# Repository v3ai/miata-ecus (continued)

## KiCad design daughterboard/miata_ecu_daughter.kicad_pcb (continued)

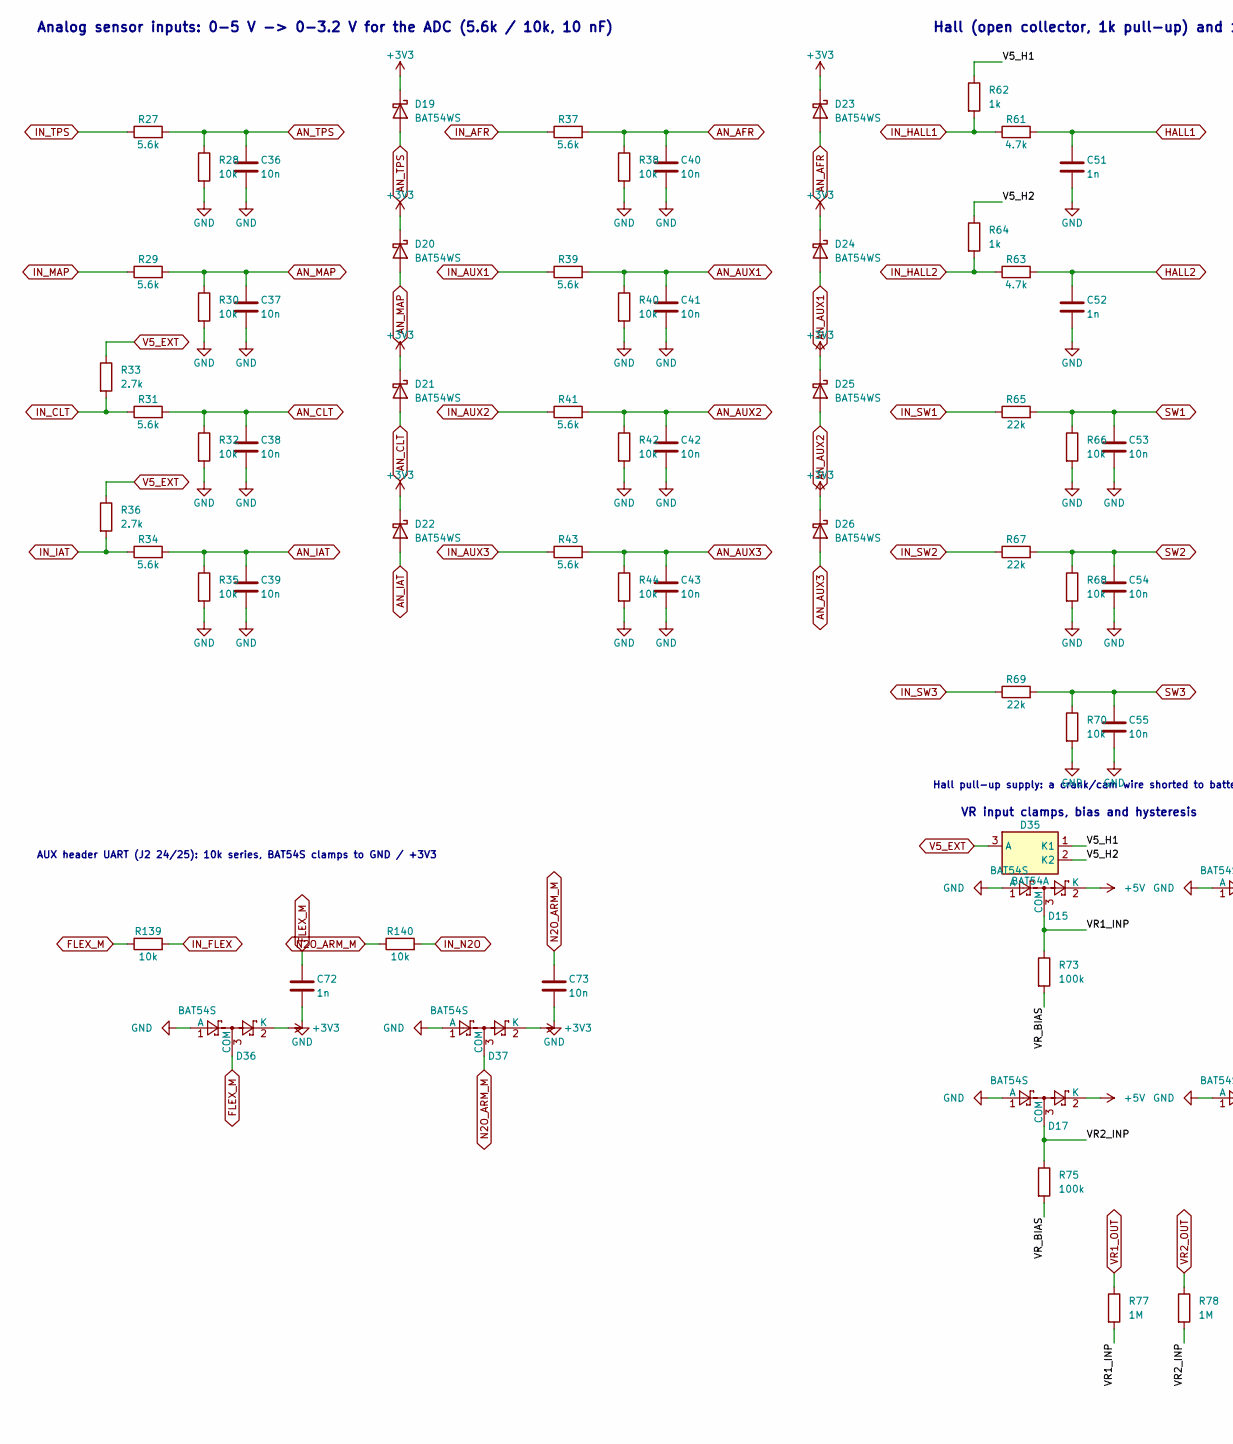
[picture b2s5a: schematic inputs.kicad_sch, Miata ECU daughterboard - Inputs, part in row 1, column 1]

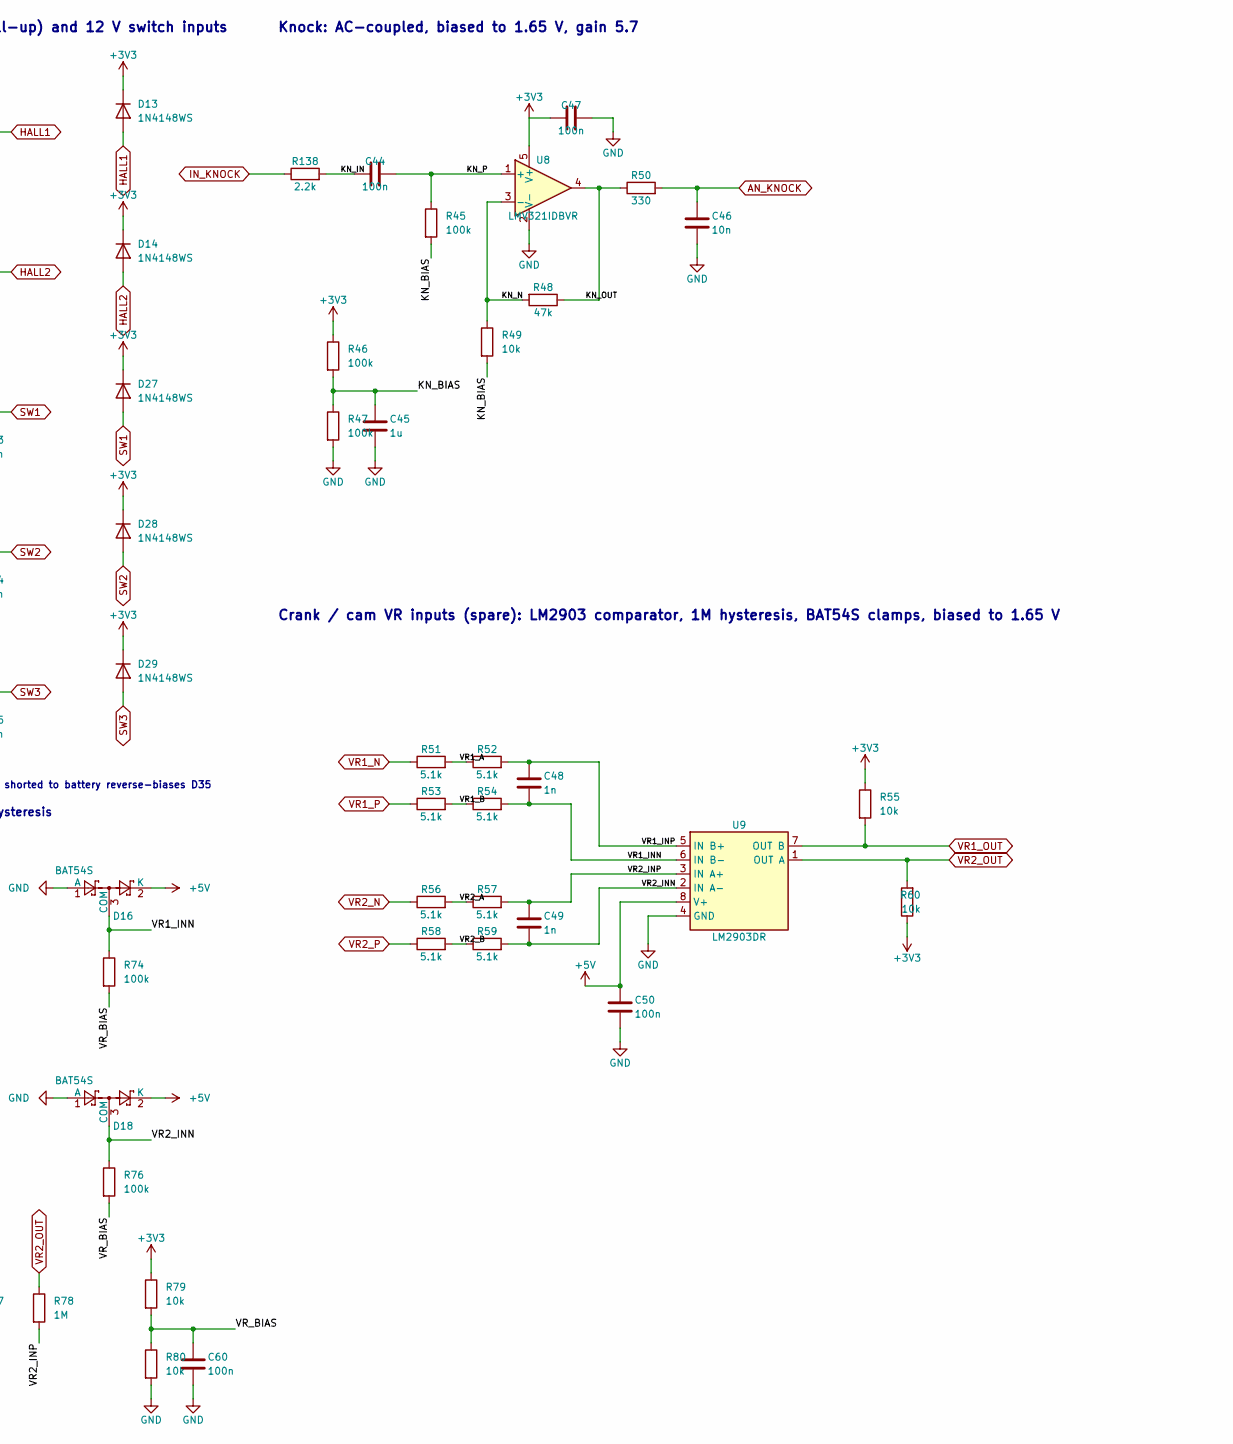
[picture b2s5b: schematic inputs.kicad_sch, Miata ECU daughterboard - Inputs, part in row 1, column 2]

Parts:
C36, C37, C38, C39, C40, C41, C42, C43, C53, C54, C55, C73: 10n; C_0402_1005Metric; LCSC C15195
C44, C47, C50: 100n; C_0603_1608Metric; LCSC C14663
C45: 1u; C_0603_1608Metric; LCSC C15849
C46: 10n; C_0603_1608Metric; LCSC C57112
C48, C49: 1n; C_0805_2012Metric; LCSC C46653
C51, C52, C72: 1n; C_0402_1005Metric; LCSC C1523
C60: 100n; C_0402_1005Metric; LCSC C1525
D13, D14, D27, D28, D29: 1N4148WS; D_SOD-323; LCSC C2128
D15, D16, D17, D18, D36, D37: BAT54S; SOT-23; LCSC C19726
D19, D20, D21, D22, D23, D24, D25, D26: BAT54WS; D_SOD-323; LCSC C124205
D35: BAT54A; SOT-23; LCSC C916423
R27, R29, R31, R34, R37, R39, R41, R43: 5.6k; R_0603_1608Metric; LCSC C23189
R28, R30, R32, R35, R38, R40, R42, R44, R66, R68, R70, R79, R80: 10k; R_0402_1005Metric; LCSC C25744
R33, R36: 2.7k; R_0603_1608Metric; LCSC C13167
R45, R46, R47: 100k; R_0603_1608Metric; LCSC C25803
R48: 47k; R_0603_1608Metric; LCSC C25819
R49, R55, R60, R139, R140: 10k; R_0603_1608Metric; LCSC C25804
R50: 330; R_0603_1608Metric; LCSC C23138
R51, R52, R53, R54, R56, R57, R58, R59: 5.1k; R_0805_2012Metric; LCSC C27834
R61, R63: 4.7k; R_0603_1608Metric; LCSC C23162
R62, R64: 1k; R_0603_1608Metric; LCSC C21190
R65, R67, R69: 22k; R_0402_1005Metric; LCSC C25768
R73, R74, R75, R76: 100k; R_0402_1005Metric; LCSC C25741
R77, R78: 1M; R_0402_1005Metric; LCSC C26083
R138: 2.2k; R_0402_1005Metric; LCSC C25879
U8: LMV321IDBVR; SOT-23-5; LCSC C7972
U9: LM2903DR; SOIC-8_3.9x4.9mm_P1.27mm; LCSC C7549

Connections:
+3V3: C47.1, D13.1 (K), D14.1 (K), D19.1 (K), D20.1 (K), D21.1 (K), D22.1 (K), D23.1 (K), D24.1 (K), D25.1 (K), D26.1 (K), D27.1 (K), D28.1 (K), D29.1 (K), D36.2 (K), D37.2 (K), R46.1, R55.1, R60.1, R79.1, U8.5 (V+); also elsewhere on the board
+5V: C50.1, D15.2 (K), D16.2 (K), D17.2 (K), D18.2 (K), U9.8 (V+); also elsewhere on the board
/Inputs/KN_BIAS: C45.1, R45.2, R46.2, R47.1, R49.2
/Inputs/KN_IN: C44.1, R138.2
/Inputs/KN_N: R48.2, R49.1, U8.3 (-)
/Inputs/KN_OUT: R48.1, R50.1, U8.4
/Inputs/KN_P: C44.2, R45.1, U8.1 (+)
/Inputs/V5_H1: D35.1 (K1), R62.1
/Inputs/V5_H2: D35.2 (K2), R64.1
/Inputs/VR1_A: R51.2, R52.1
/Inputs/VR1_B: R53.2, R54.1
/Inputs/VR1_INN: C48.2, D16.3 (COM), R54.2, R74.1, U9.6 (IN B-)
/Inputs/VR1_INP: C48.1, D15.3 (COM), R52.2, R73.1, R77.2, U9.5 (IN B+)
/Inputs/VR2_A: R56.2, R57.1
/Inputs/VR2_B: R58.2, R59.1
/Inputs/VR2_INN: C49.2, D18.3 (COM), R59.2, R76.1, U9.2 (IN A-)
/Inputs/VR2_INP: C49.1, D17.3 (COM), R57.2, R75.1, R78.2, U9.3 (IN A+)
/Inputs/VR_BIAS: C60.1, R73.2, R74.2, R75.2, R76.2, R79.2, R80.1
AN_AFR: C40.1, D23.2 (A), R37.2, R38.1; also elsewhere on the board
AN_AUX1: C41.1, D24.2 (A), R39.2, R40.1; also elsewhere on the board
AN_AUX2: C42.1, D25.2 (A), R41.2, R42.1; also elsewhere on the board
AN_AUX3: C43.1, D26.2 (A), R43.2, R44.1; also elsewhere on the board
AN_CLT: C38.1, D21.2 (A), R31.2, R32.1; also elsewhere on the board
AN_IAT: C39.1, D22.2 (A), R34.2, R35.1; also elsewhere on the board
AN_KNOCK: C46.1, R50.2; also elsewhere on the board
AN_MAP: C37.1, D20.2 (A), R29.2, R30.1; also elsewhere on the board
AN_TPS: C36.1, D19.2 (A), R27.2, R28.1; also elsewhere on the board
FLEX_M: C72.1, D36.3 (COM), R139.1; also elsewhere on the board
GND: C36.2, C37.2, C38.2, C39.2, C40.2, C41.2, C42.2, C43.2, C45.2, C46.2, C47.2, C50.2, C51.2, C52.2, C53.2, C54.2, C55.2, C60.2, C72.2, C73.2, D15.1 (A), D16.1 (A), D17.1 (A), D18.1 (A), D36.1 (A), D37.1 (A), R28.2, R30.2, R32.2, R35.2, R38.2, R40.2, R42.2, R44.2, R47.2, R66.2, R68.2, R70.2, R80.2, U8.2 (V-), U9.4 (GND); also elsewhere on the board
HALL1: C51.1, D13.2 (A), R61.2; also elsewhere on the board
HALL2: C52.1, D14.2 (A), R63.2; also elsewhere on the board
IN_AFR: R37.1; also elsewhere on the board
IN_AUX1: R39.1; also elsewhere on the board
IN_AUX2: R41.1; also elsewhere on the board
IN_AUX3: R43.1; also elsewhere on the board
IN_CLT: R31.1, R33.2; also elsewhere on the board
IN_FLEX: R139.2; also elsewhere on the board
IN_HALL1: R61.1, R62.2; also elsewhere on the board
IN_HALL2: R63.1, R64.2; also elsewhere on the board
IN_IAT: R34.1, R36.2; also elsewhere on the board
IN_KNOCK: R138.1; also elsewhere on the board
IN_MAP: R29.1; also elsewhere on the board
IN_N2O: R140.2; also elsewhere on the board
IN_SW1: R65.1; also elsewhere on the board
IN_SW2: R67.1; also elsewhere on the board
IN_SW3: R69.1; also elsewhere on the board
IN_TPS: R27.1; also elsewhere on the board
N2O_ARM_M: C73.1, D37.3 (COM), R140.1; also elsewhere on the board
SW1: C53.1, D27.2 (A), R65.2, R66.1; also elsewhere on the board
SW2: C54.1, D28.2 (A), R67.2, R68.1; also elsewhere on the board
SW3: C55.1, D29.2 (A), R69.2, R70.1; also elsewhere on the board
V5_EXT: D35.3 (A), R33.1, R36.1; also elsewhere on the board
VR1_N: R51.1; also elsewhere on the board
VR1_OUT: R55.2, R77.1, U9.7 (OUT B); also elsewhere on the board
VR1_P: R53.1; also elsewhere on the board
VR2_N: R56.1; also elsewhere on the board
VR2_OUT: R60.2, R78.1, U9.1 (OUT A); also elsewhere on the board
VR2_P: R58.1; also elsewhere on the board

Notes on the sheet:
Analog sensor inputs: 0-5 V -> 0-3.2 V for the ADC (5.6k / 10k, 10 nF)
Hall (open collector, 1k pull-up) and 12 V switch inputs
Hall pull-up supply: a crank/cam wire shorted to battery reverse-biases D35
AUX header UART (J2 24/25): 10k series, BAT54S clamps to GND / +3V3
Knock: AC-coupled, biased to 1.65 V, gain 5.7
Crank / cam VR inputs (spare): LM2903 comparator, 1M hysteresis, BAT54S clamps, biased to 1.65 V
VR input clamps, bias and hysteresis

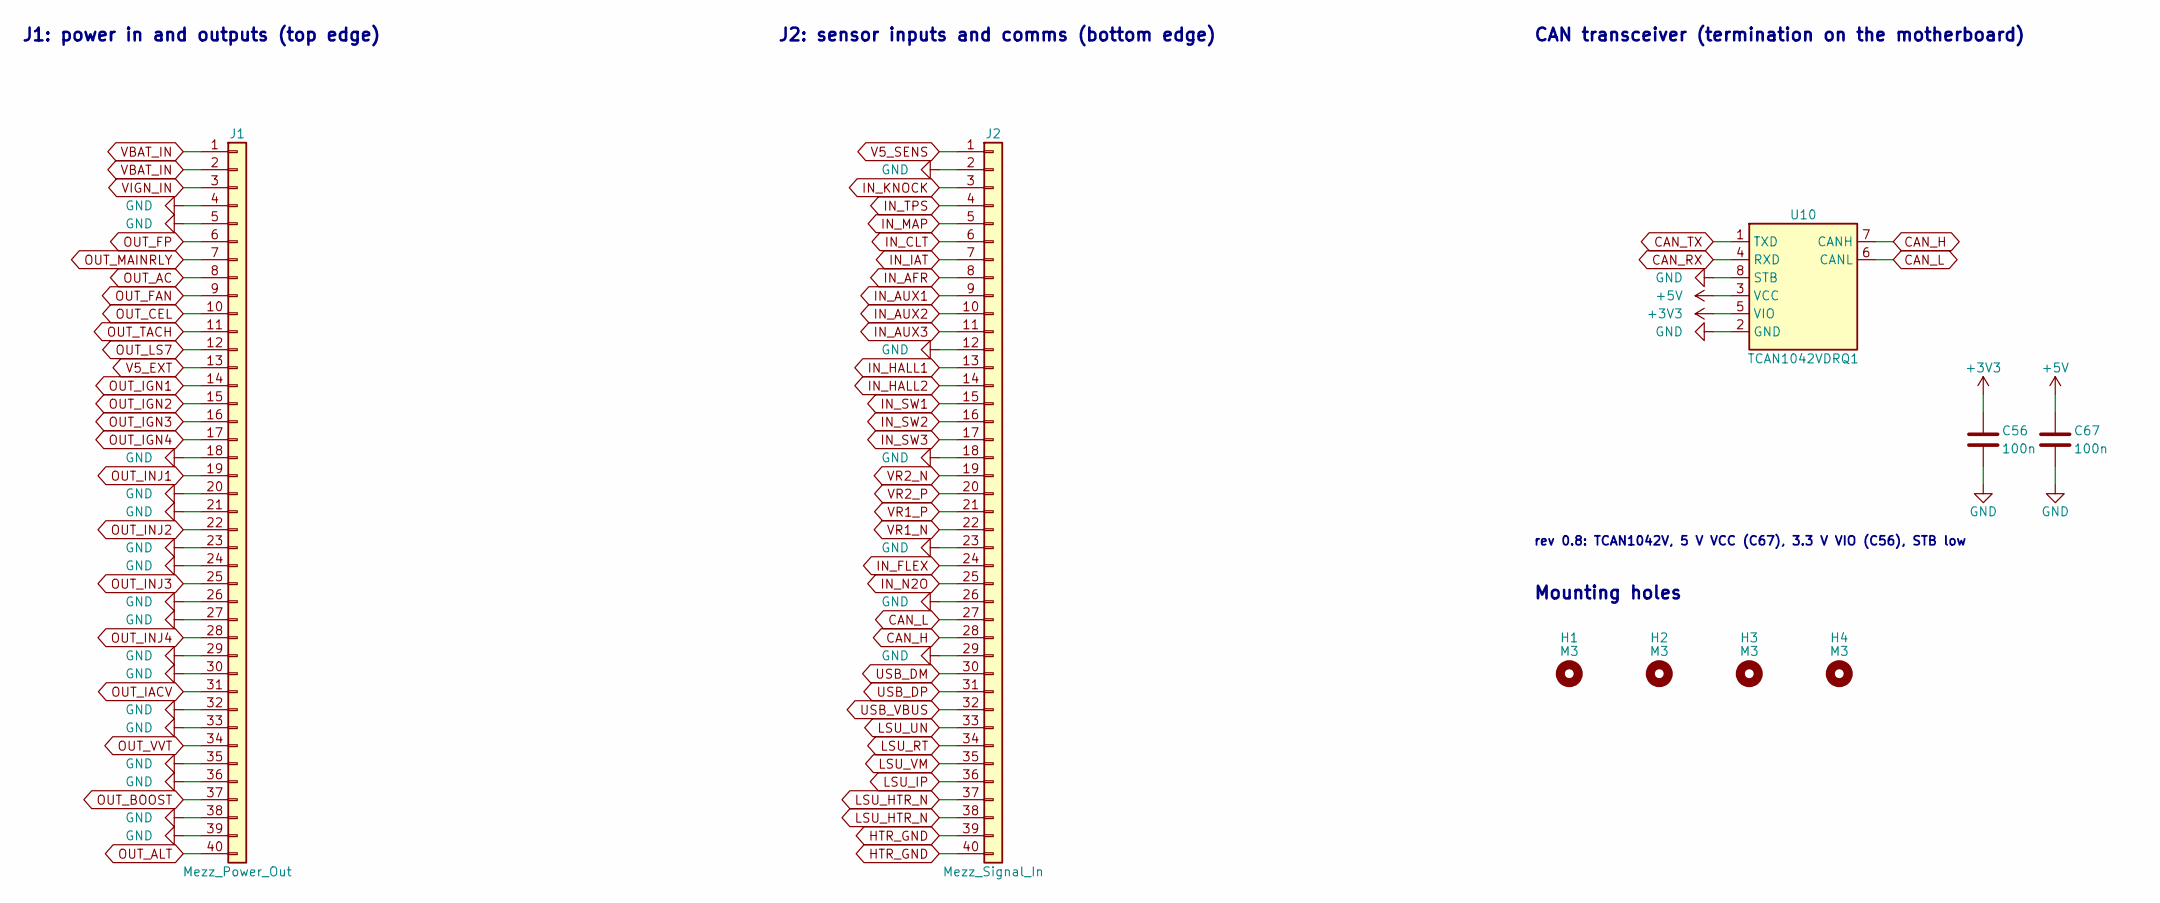
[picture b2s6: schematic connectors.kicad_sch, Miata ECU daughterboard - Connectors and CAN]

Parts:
C56: 100n; C_0603_1608Metric; LCSC C14663
C67: 100n; C_0402_1005Metric; LCSC C1525
H1, H2, H3, H4: M3; MountingHole_3.2mm_M3
J1: Mezz_Power_Out; PinHeader_1x40_P2.54mm_Vertical; LCSC C2977586
J2: Mezz_Signal_In; PinHeader_1x40_P2.54mm_Vertical; LCSC C2977586
U10: TCAN1042VDRQ1; SOIC-8_3.9x4.9mm_P1.27mm; LCSC C485806

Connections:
+3V3: C56.1, U10.5 (VIO); also elsewhere on the board
+5V: C67.1, U10.3 (VCC); also elsewhere on the board
CAN_H: J2.28, U10.7 (CANH); also elsewhere on the board
CAN_L: J2.27, U10.6 (CANL); also elsewhere on the board
CAN_RX: U10.4 (RXD); also elsewhere on the board
CAN_TX: U10.1 (TXD); also elsewhere on the board
GND: C56.2, C67.2, J1.4, J1.5, J1.18, J1.20, J1.21, J1.23, J1.24, J1.26, J1.27, J1.29, J1.30, J1.32, J1.33, J1.35, J1.36, J1.38, J1.39, J2.2, J2.12, J2.18, J2.23, J2.26, J2.29, U10.2 (GND), U10.8 (STB); also elsewhere on the board
HTR_GND: J2.39, J2.40; also elsewhere on the board
IN_AFR: J2.8; also elsewhere on the board
IN_AUX1: J2.9; also elsewhere on the board
IN_AUX2: J2.10; also elsewhere on the board
IN_AUX3: J2.11; also elsewhere on the board
IN_CLT: J2.6; also elsewhere on the board
IN_FLEX: J2.24; also elsewhere on the board
IN_HALL1: J2.13; also elsewhere on the board
IN_HALL2: J2.14; also elsewhere on the board
IN_IAT: J2.7; also elsewhere on the board
IN_KNOCK: J2.3; also elsewhere on the board
IN_MAP: J2.5; also elsewhere on the board
IN_N2O: J2.25; also elsewhere on the board
IN_SW1: J2.15; also elsewhere on the board
IN_SW2: J2.16; also elsewhere on the board
IN_SW3: J2.17; also elsewhere on the board
IN_TPS: J2.4; also elsewhere on the board
LSU_HTR_N: J2.37, J2.38; also elsewhere on the board
LSU_IP: J2.36; also elsewhere on the board
LSU_RT: J2.34; also elsewhere on the board
LSU_UN: J2.33; also elsewhere on the board
LSU_VM: J2.35; also elsewhere on the board
OUT_AC: J1.8; also elsewhere on the board
OUT_ALT: J1.40; also elsewhere on the board
OUT_BOOST: J1.37; also elsewhere on the board
OUT_CEL: J1.10; also elsewhere on the board
OUT_FAN: J1.9; also elsewhere on the board
OUT_FP: J1.6; also elsewhere on the board
OUT_IACV: J1.31; also elsewhere on the board
OUT_IGN1: J1.14; also elsewhere on the board
OUT_IGN2: J1.15; also elsewhere on the board
OUT_IGN3: J1.16; also elsewhere on the board
OUT_IGN4: J1.17; also elsewhere on the board
OUT_INJ1: J1.19; also elsewhere on the board
OUT_INJ2: J1.22; also elsewhere on the board
OUT_INJ3: J1.25; also elsewhere on the board
OUT_INJ4: J1.28; also elsewhere on the board
OUT_LS7: J1.12; also elsewhere on the board
OUT_MAINRLY: J1.7; also elsewhere on the board
OUT_TACH: J1.11; also elsewhere on the board
OUT_VVT: J1.34; also elsewhere on the board
USB_DM: J2.30; also elsewhere on the board
USB_DP: J2.31; also elsewhere on the board
USB_VBUS: J2.32; also elsewhere on the board
V5_EXT: J1.13; also elsewhere on the board
V5_SENS: J2.1; also elsewhere on the board
VBAT_IN: J1.1, J1.2; also elsewhere on the board
VIGN_IN: J1.3; also elsewhere on the board
VR1_N: J2.22; also elsewhere on the board
VR1_P: J2.21; also elsewhere on the board
VR2_N: J2.19; also elsewhere on the board
VR2_P: J2.20; also elsewhere on the board

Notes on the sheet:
J1: power in and outputs (top edge)
J2: sensor inputs and comms (bottom edge)
CAN transceiver (termination on the motherboard)
rev 0.8: TCAN1042V, 5 V VCC (C67), 3.3 V VIO (C56), STB low
Mounting holes

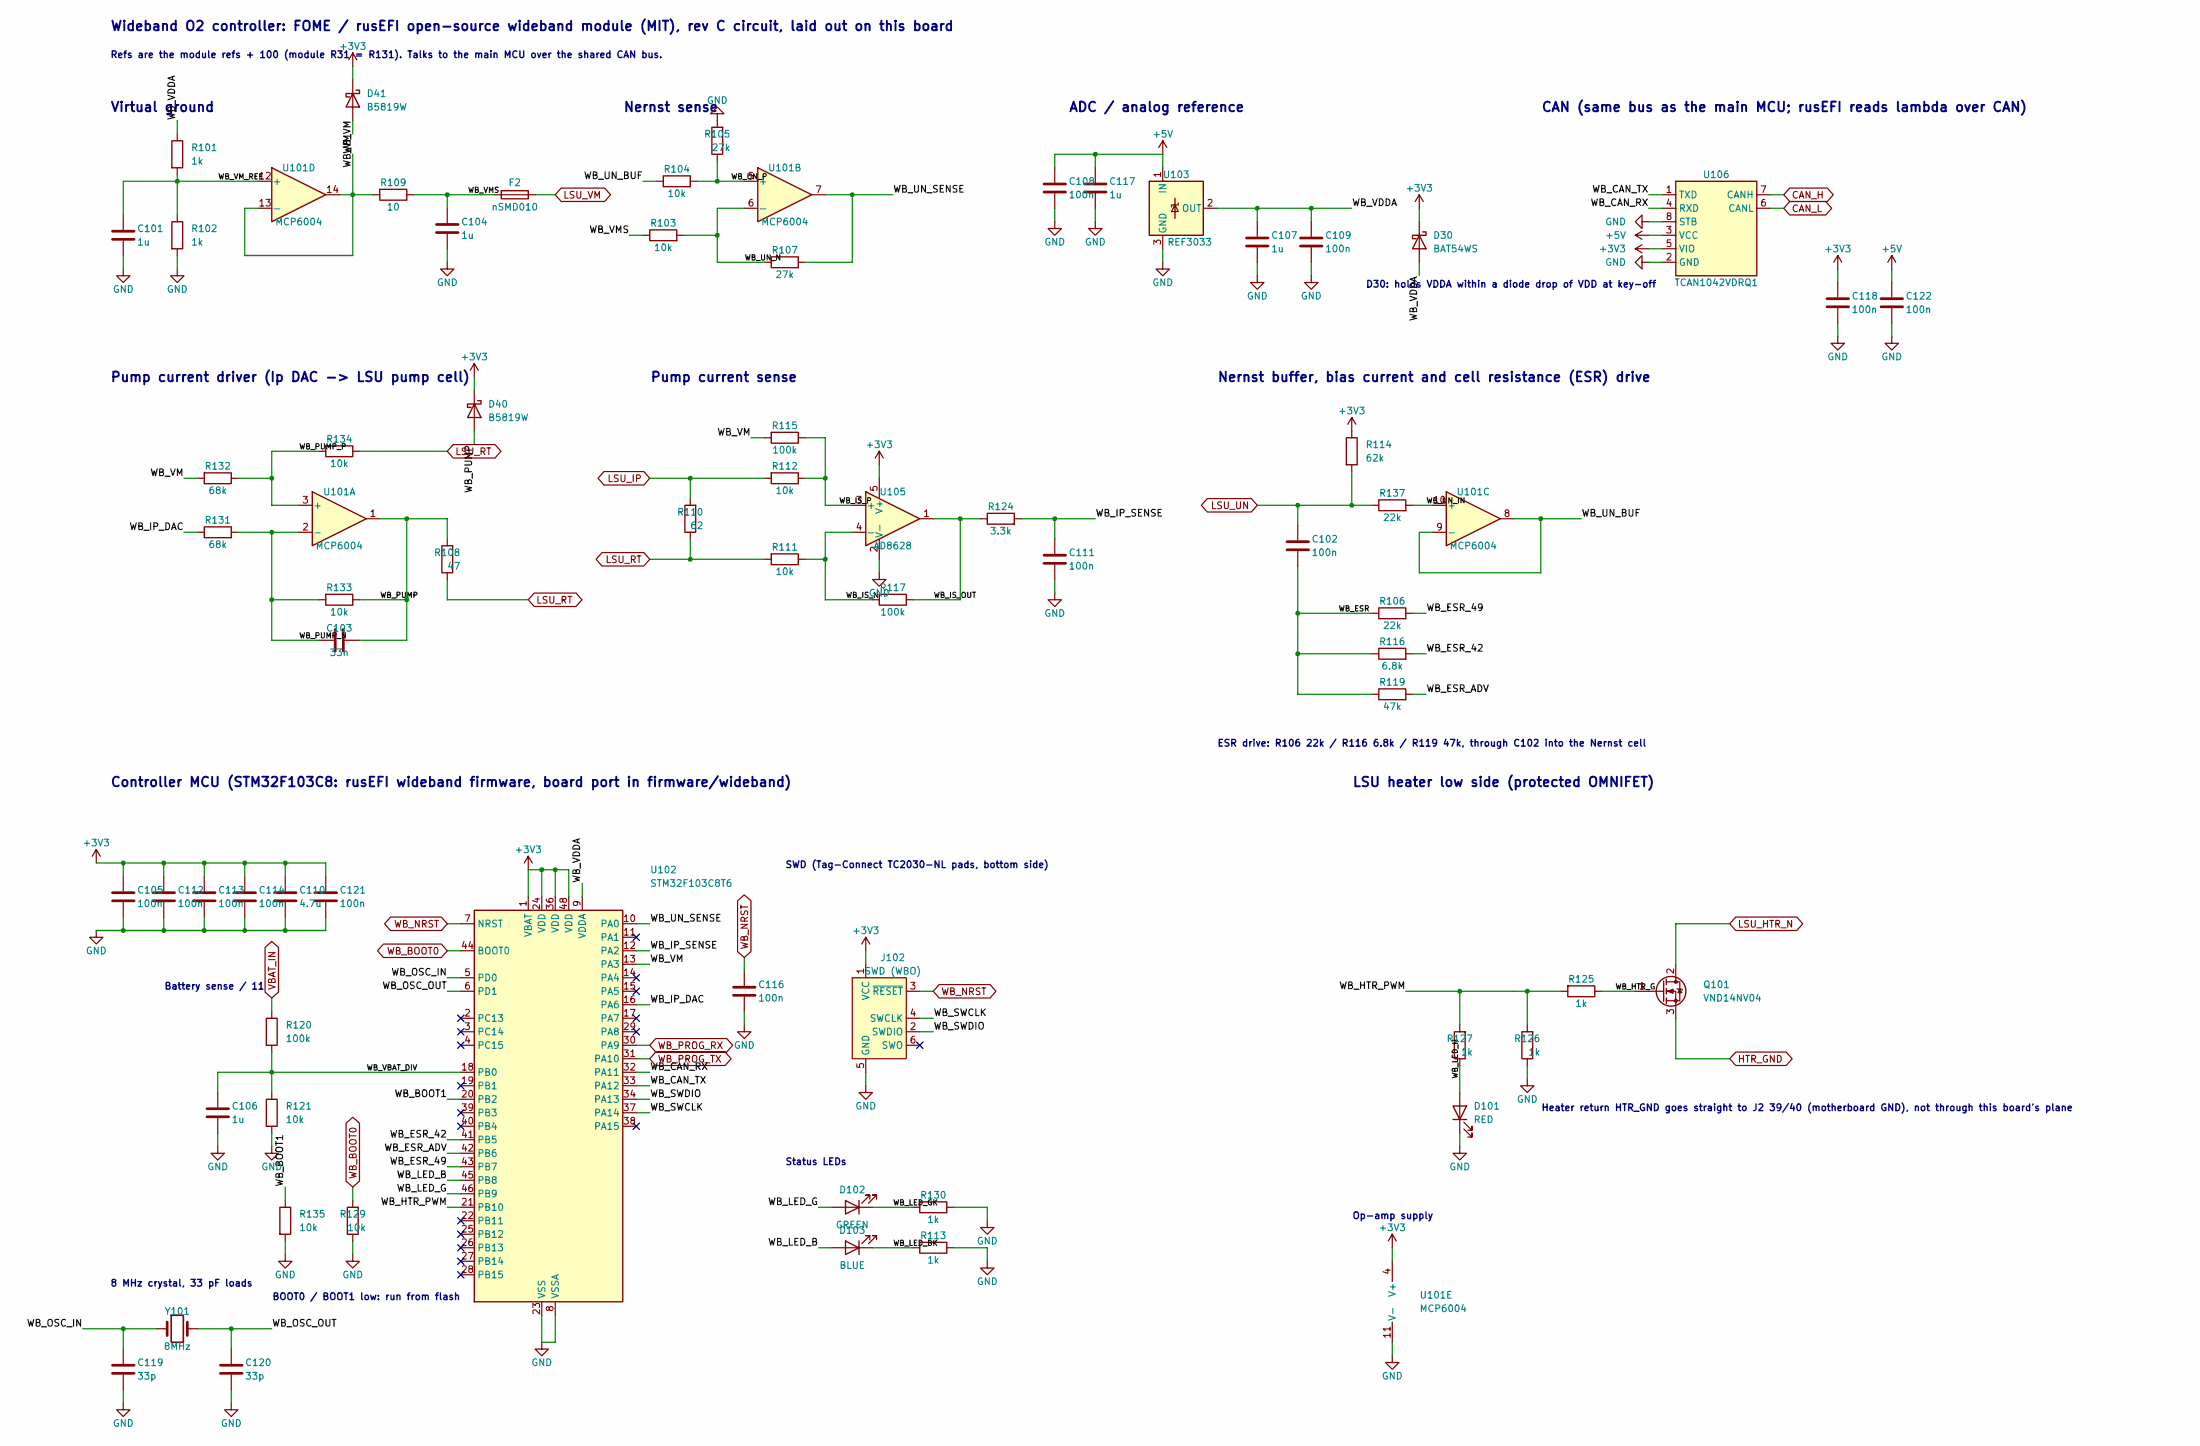
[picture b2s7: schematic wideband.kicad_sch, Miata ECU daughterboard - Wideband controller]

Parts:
C101, C104, C106, C107, C117: 1u; C_0402_1005Metric; LCSC C52923
C102, C105, C108, C109, C111, C112, C113, C114, C116, C118, C121, C122: 100n; C_0402_1005Metric; LCSC C1525
C103: 33n; C_0402_1005Metric; LCSC C106862
C110: 4.7u; C_0603_1608Metric; LCSC C19666
C119, C120: 33p; C_0402_1005Metric; LCSC C1562
D30: BAT54WS; D_SOD-323; LCSC C124205
D40, D41: B5819W; D_SOD-123; LCSC C8598
D101: RED; LED_0603_1608Metric; LCSC C2286
D102: GREEN; LED_0603_1608Metric; LCSC C12624
D103: BLUE; LED_0603_1608Metric; LCSC C2288
F2: nSMD010; Fuse_1206_3216Metric; LCSC C70065
J102: SWD (WBO); Tag-Connect_TC2030-IDC-NL_2x03_P1.27mm_Vertical
Q101: VND14NV04; TO-252-2; LCSC C2649436
R101, R102, R113, R125, R126, R127, R130: 1k; R_0402_1005Metric; LCSC C11702
R103, R104, R111, R112, R121, R129, R133, R134, R135: 10k; R_0402_1005Metric; LCSC C25744
R105, R107: 27k; R_0402_1005Metric; LCSC C25771
R106, R137: 22k; R_0402_1005Metric; LCSC C25768
R108: 47; R_1206_3216Metric; LCSC C17969
R109: 10; R_1206_3216Metric; LCSC C17903
R110: 62; R_1206_3216Metric; LCSC C25341
R114: 62k; R_0603_1608Metric; LCSC C23221
R115, R117, R120: 100k; R_0402_1005Metric; LCSC C25741
R116: 6.8k; R_0402_1005Metric; LCSC C25917
R119: 47k; R_0402_1005Metric; LCSC C25792
R124: 3.3k; R_0402_1005Metric; LCSC C25890
R131, R132: 68k; R_0402_1005Metric; LCSC C36871
U101: MCP6004; TSSOP-14_4.4x5mm_P0.65mm; LCSC C50282
U102: STM32F103C8T6; LQFP-48_7x7mm_P0.5mm; LCSC C8734
U103: REF3033; SOT-23; LCSC C36658
U105: AD8628; SOT-23-5; LCSC C29309
U106: TCAN1042VDRQ1; SOIC-8_3.9x4.9mm_P1.27mm; LCSC C485806
Y101: 8MHz; Crystal_SMD_5032-2Pin_5.0x3.2mm; LCSC C115962

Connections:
+3V3: C105.1, C110.1, C112.1, C113.1, C114.1, C118.1, C121.1, D30.1 (K), D40.1 (K), D41.1 (K), J102.1 (VCC), R114.1, U101.4 (V+), U102.1 (VBAT), U102.24 (VDD), U102.36 (VDD), U102.48 (VDD), U105.5 (V+), U106.5 (VIO); also elsewhere on the board
+5V: C108.1, C117.1, C122.1, U103.1 (IN), U106.3 (VCC); also elsewhere on the board
/Wideband controller/WB_BOOT1: R135.1, U102.20 (PB2)
/Wideband controller/WB_CAN_RX: U102.32 (PA11), U106.4 (RXD)
/Wideband controller/WB_CAN_TX: U102.33 (PA12), U106.1 (TXD)
/Wideband controller/WB_ESR: C102.2, R106.1, R116.1, R119.1
/Wideband controller/WB_ESR_42: R116.2, U102.41 (PB5)
/Wideband controller/WB_ESR_49: R106.2, U102.43 (PB7)
/Wideband controller/WB_ESR_ADV: R119.2, U102.42 (PB6)
/Wideband controller/WB_HTR_G: Q101.1 (G), R125.1
/Wideband controller/WB_HTR_PWM: R125.2, R126.2, R127.2, U102.21 (PB10)
/Wideband controller/WB_IP_DAC: R131.1, U102.16 (PA6)
/Wideband controller/WB_IP_SENSE: C111.1, R124.2, U102.12 (PA2)
/Wideband controller/WB_IS_N: R111.1, R117.2, U105.4 (-)
/Wideband controller/WB_IS_OUT: R117.1, R124.1, U105.1
/Wideband controller/WB_IS_P: R112.1, R115.1, U105.3 (+)
/Wideband controller/WB_LED_B: D103.2 (A), U102.45 (PB8)
/Wideband controller/WB_LED_BK: D103.1 (K), R113.2
/Wideband controller/WB_LED_G: D102.2 (A), U102.46 (PB9)
/Wideband controller/WB_LED_GK: D102.1 (K), R130.2
/Wideband controller/WB_LED_H: D101.2 (A), R127.1
/Wideband controller/WB_OSC_IN: C119.1, U102.5 (PD0), Y101.1
/Wideband controller/WB_OSC_OUT: C120.1, U102.6 (PD1), Y101.2
/Wideband controller/WB_PUMP: C103.1, D40.2 (A), R108.2, R133.1, U101.1
/Wideband controller/WB_PUMP_N: C103.2, R131.2, R133.2, U101.2 (-)
/Wideband controller/WB_PUMP_P: R132.1, R134.2, U101.3 (+)
/Wideband controller/WB_SWCLK: J102.4 (SWCLK), U102.37 (PA14)
/Wideband controller/WB_SWDIO: J102.2 (SWDIO), U102.34 (PA13)
/Wideband controller/WB_UN_BUF: R104.1, U101.8, U101.9 (-)
/Wideband controller/WB_UN_IN: R137.2, U101.10 (+)
/Wideband controller/WB_UN_N: R103.2, R107.1, U101.6 (-)
/Wideband controller/WB_UN_P: R104.2, R105.1, U101.5 (+)
/Wideband controller/WB_UN_SENSE: R107.2, U101.7, U102.10 (PA0)
/Wideband controller/WB_VBAT_DIV: C106.1, R120.2, R121.1, U102.18 (PB0)
/Wideband controller/WB_VDDA: C107.1, C109.1, D30.2 (A), R101.1, U102.9 (VDDA), U103.2 (OUT)
/Wideband controller/WB_VM: D41.2 (A), R109.2, R115.2, R132.2, U101.13 (-), U101.14, U102.13 (PA3)
/Wideband controller/WB_VMS: C104.1, F2.2, R103.1, R109.1
/Wideband controller/WB_VM_REF: C101.1, R101.2, R102.1, U101.12 (+)
CAN_H: U106.7 (CANH); also elsewhere on the board
CAN_L: U106.6 (CANL); also elsewhere on the board
GND: C101.2, C104.2, C105.2, C106.2, C107.2, C108.2, C109.2, C110.2, C111.2, C112.2, C113.2, C114.2, C116.2, C117.2, C118.2, C119.2, C120.2, C121.2, C122.2, D101.1 (K), J102.5 (GND), R102.2, R105.2, R113.1, R121.2, R126.1, R129.1, R130.1, R135.2, U101.11 (V-), U102.8 (VSSA), U102.23 (VSS), U102.35 (VSS), U102.47 (VSS), U103.3 (GND), U105.2 (V-), U106.2 (GND), U106.8 (STB); also elsewhere on the board
HTR_GND: Q101.3 (S); also elsewhere on the board
LSU_HTR_N: Q101.2 (D); also elsewhere on the board
LSU_IP: R110.2, R112.2; also elsewhere on the board
LSU_RT: R108.1, R110.1, R111.2, R134.1; also elsewhere on the board
LSU_UN: C102.1, R114.2, R137.1; also elsewhere on the board
LSU_VM: F2.1; also elsewhere on the board
VBAT_IN: R120.1; also elsewhere on the board
WB_BOOT0: R129.2, U102.44 (BOOT0); also elsewhere on the board
WB_NRST: C116.1, J102.3 (~RESET), U102.7 (NRST); also elsewhere on the board
WB_PROG_RX: U102.30 (PA9); also elsewhere on the board
WB_PROG_TX: U102.31 (PA10); also elsewhere on the board

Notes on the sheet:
Wideband O2 controller: FOME / rusEFI open-source wideband module (MIT), rev C circuit, laid out on this board
Refs are the module refs + 100 (module R31 = R131). Talks to the main MCU over the shared CAN bus.
Virtual ground
Nernst sense
ADC / analog reference
D30: holds VDDA within a diode drop of VDD at key-off
CAN (same bus as the main MCU; rusEFI reads lambda over CAN)
Pump current driver (Ip DAC -> LSU pump cell)
Pump current sense
Nernst buffer, bias current and cell resistance (ESR) drive
ESR drive: R106 22k / R116 6.8k / R119 47k, through C102 into the Nernst cell
Controller MCU (STM32F103C8: rusEFI wideband firmware, board port in firmware/wideband)
BOOT0 / BOOT1 low: run from flash
Battery sense / 11
8 MHz crystal, 33 pF loads
Status LEDs
SWD (Tag-Connect TC2030-NL pads, bottom side)
LSU heater low side (protected OMNIFET)
Heater return HTR_GND goes straight to J2 39/40 (motherboard GND), not through this board's plane
Op-amp supply
